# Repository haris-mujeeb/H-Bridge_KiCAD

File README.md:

# H-Bridge

## Components:
- 4N25 - 6 PIN DIP PHOTOTRANSISTOR PHOTOCOUPLER 
- AO3401A - P-Channel MOSFETs
- FDS6630A - N-Channel MOSFET
- 0805 SMD Resistors
- 2.54mm PinHeader Vertical Connectors 01x02
- 2.54mm PinHeader Vertical Connectors 01x01

## Screenshots

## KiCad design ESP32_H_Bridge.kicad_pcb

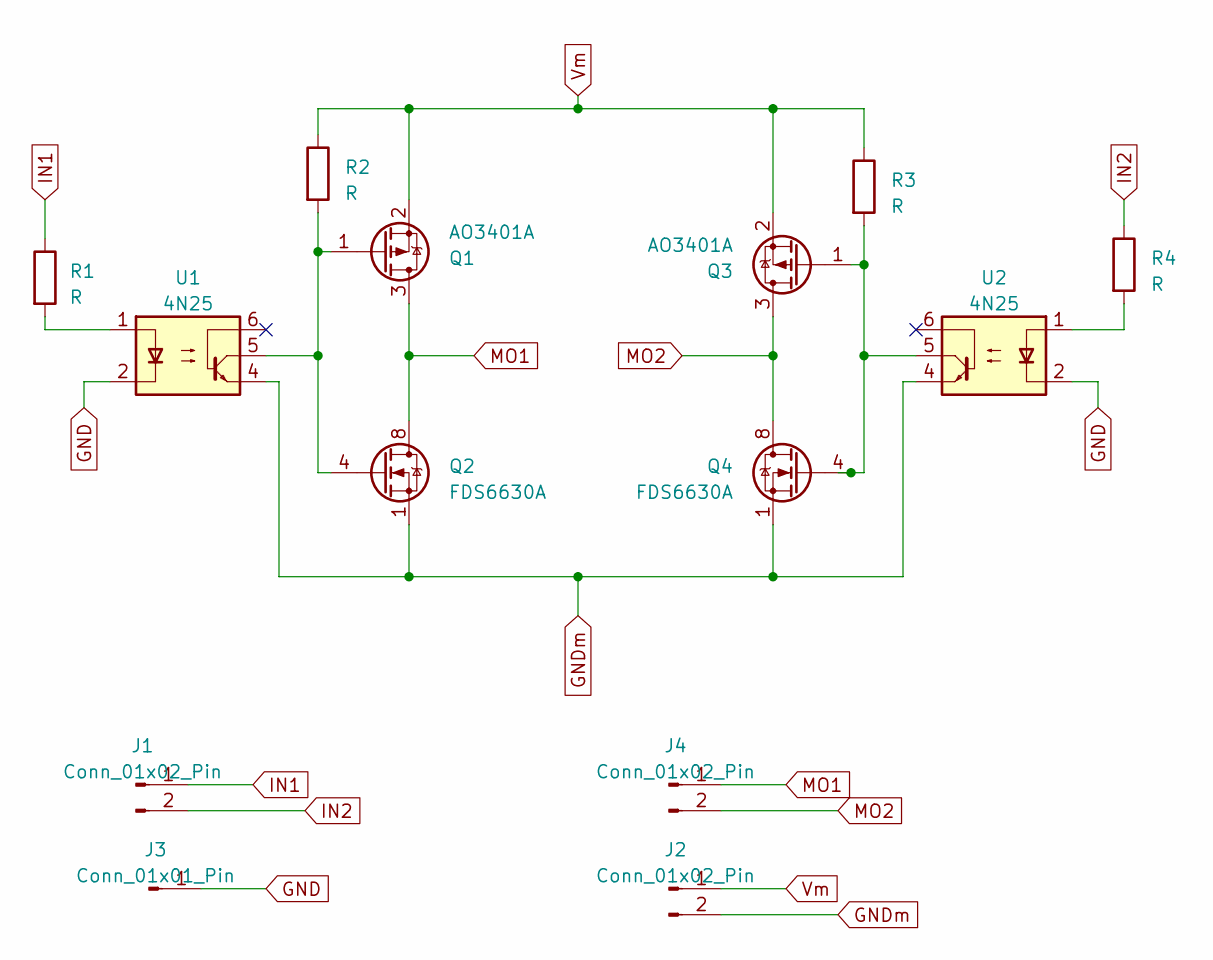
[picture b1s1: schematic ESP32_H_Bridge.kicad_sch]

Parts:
J1, J2, J4: Conn_01x02_Pin; PinHeader_1x02_P2.54mm_Vertical
J3: Conn_01x01_Pin; PinHeader_1x01_P2.54mm_Vertical
Q1, Q3: AO3401A; SOT-23
Q2, Q4: FDS6630A; SOIC-8_3.9x4.9mm_P1.27mm
R1, R2, R3, R4: R; R_0805_2012Metric_Pad1.20x1.40mm_HandSolder
U1, U2: 4N25; DIP-6_W7.62mm

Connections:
GND: J3.1, U1.2, U2.2
GNDm: J2.2, Q2.1 (S), Q2.2 (S), Q2.3 (S), Q4.1 (S), Q4.2 (S), Q4.3 (S), U1.4, U2.4
IN1: J1.1, R1.1
IN2: J1.2, R4.1
MO1: J4.1, Q1.3 (D), Q2.5 (D), Q2.6 (D), Q2.7 (D), Q2.8 (D)
MO2: J4.2, Q3.3 (D), Q4.5 (D), Q4.6 (D), Q4.7 (D), Q4.8 (D)
unnamed: Q1.1 (G), Q2.4 (G), R2.2, U1.5
unnamed: Q3.1 (G), Q4.4 (G), R3.2, U2.5
unnamed: R1.2, U1.1
unnamed: R4.2, U2.1
Vm: J2.1, Q1.2 (S), Q3.2 (S), R2.1, R3.1

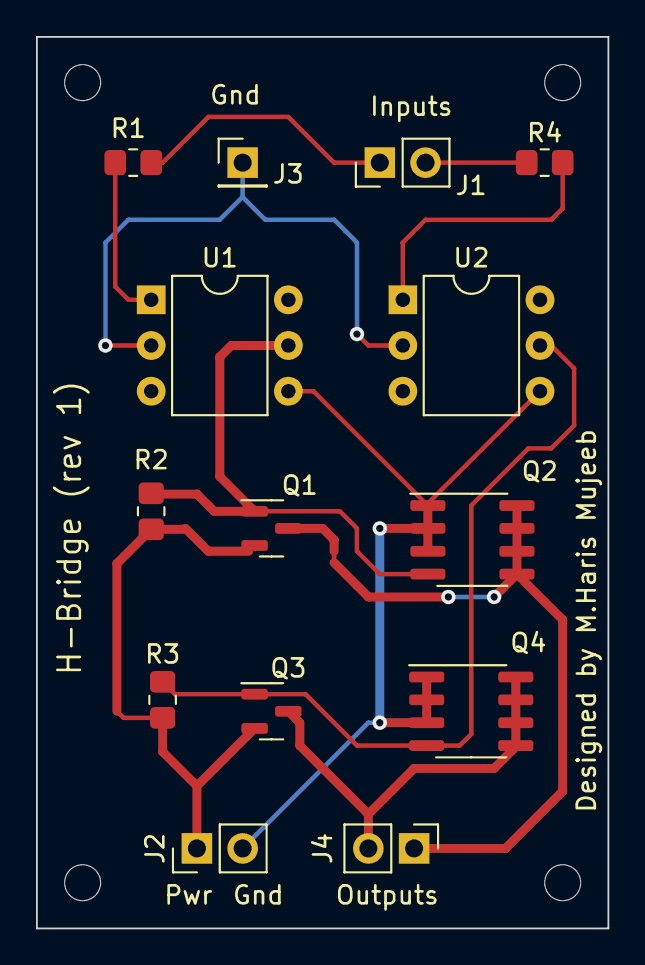
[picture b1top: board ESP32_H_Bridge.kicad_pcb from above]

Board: 2 copper layers, 31.8 x 49.5 mm, 14 parts (0 on the bottom side), 11 nets.
